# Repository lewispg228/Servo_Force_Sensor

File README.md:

# Servo_Force_Sensor
A small PCB with a hall effect sensor that can sense very slight movement of a magnet on a servo horn.

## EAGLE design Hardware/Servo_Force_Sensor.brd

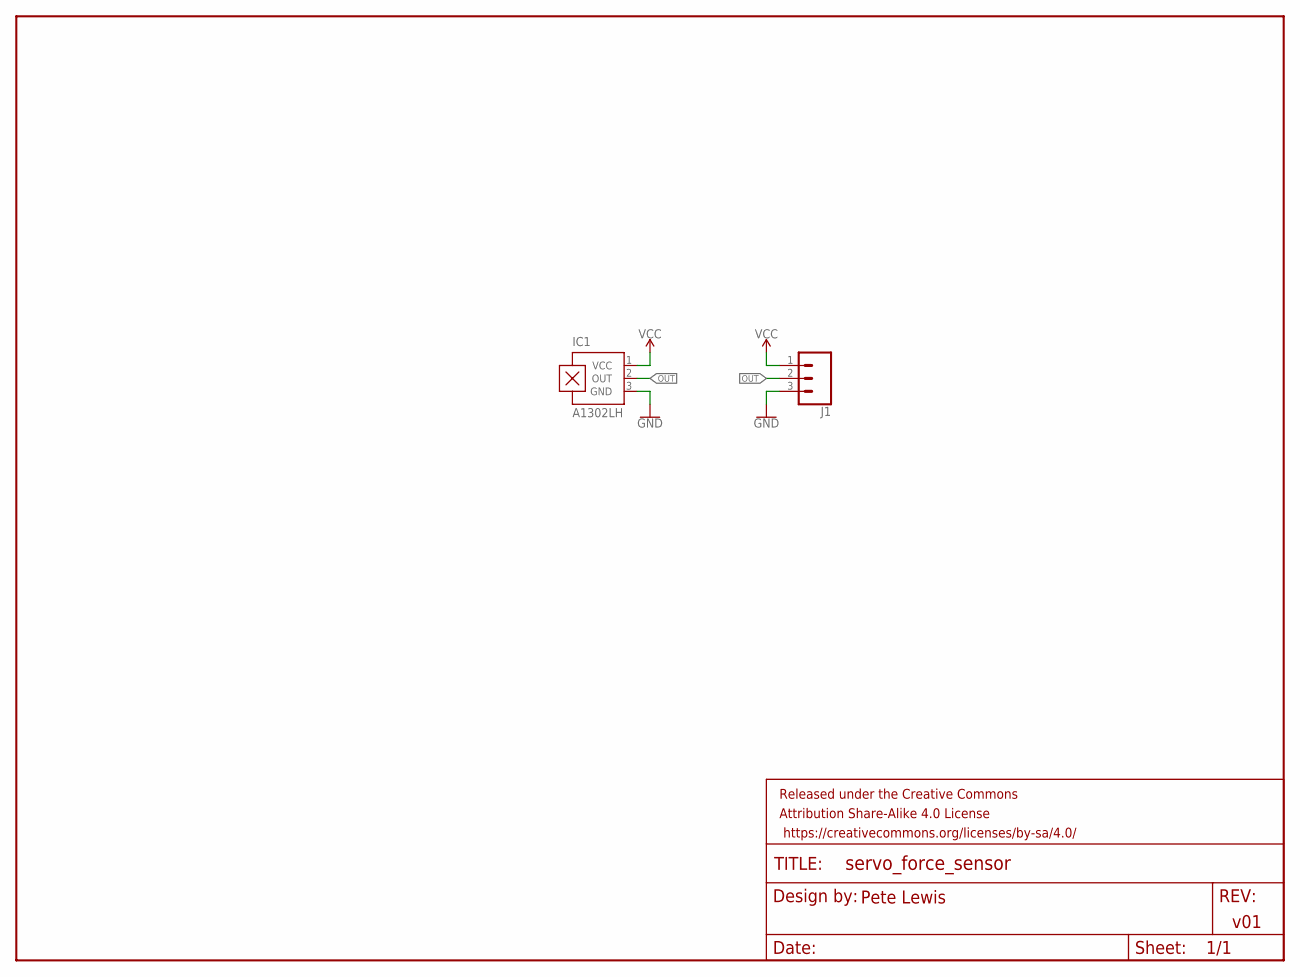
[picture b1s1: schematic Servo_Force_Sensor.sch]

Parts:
FRAME1: FRAME-LETTER; CREATIVE_COMMONS
IC1: A1302LH; SOT23-W
J1: CONN_03LONGPADS; 1X03_LONGPADS

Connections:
GND: IC1.3 (GND), J1.3
OUT: IC1.2 (OUT), J1.2
VCC: IC1.1 (VCC), J1.1

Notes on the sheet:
v01
Pete Lewis

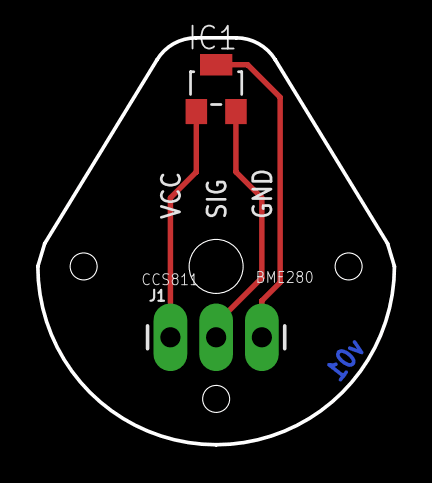
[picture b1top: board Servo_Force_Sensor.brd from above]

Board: 2 copper layers, 19.8 x 22.6 mm, 4 parts (0 on the bottom side), 3 nets.

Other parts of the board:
U$1: MEDIUM_HORN_16MM

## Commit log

2019-06-13 blanks slate eagle files and gitignore
2019-06-17 library work for medium and large horns
2019-06-19 finalized v01
    outer shape done,
    verified drill holes via lazer cut acrylic prototype
2019-06-20 started controller layout - dimensional planning only
    used servo from wonka lbr - not verified, but probably pretty close cuz I used it on a testbed that worked out.
2019-06-20 started tray design
2019-09-16 ADC readings test sketch

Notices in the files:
parts and their libraries:
SparkFun-Aesthetics: Licensing: Creative Commons ShareAlike 4.0 International - https://creativecommons.org/licenses/by-sa/4.0
SparkFun-Aesthetics: Released under the Creative Commons Attribution Share-Alike 4.0 License
SparkFun-Aesthetics: https://creativecommons.org/licenses/by-sa/4.0
